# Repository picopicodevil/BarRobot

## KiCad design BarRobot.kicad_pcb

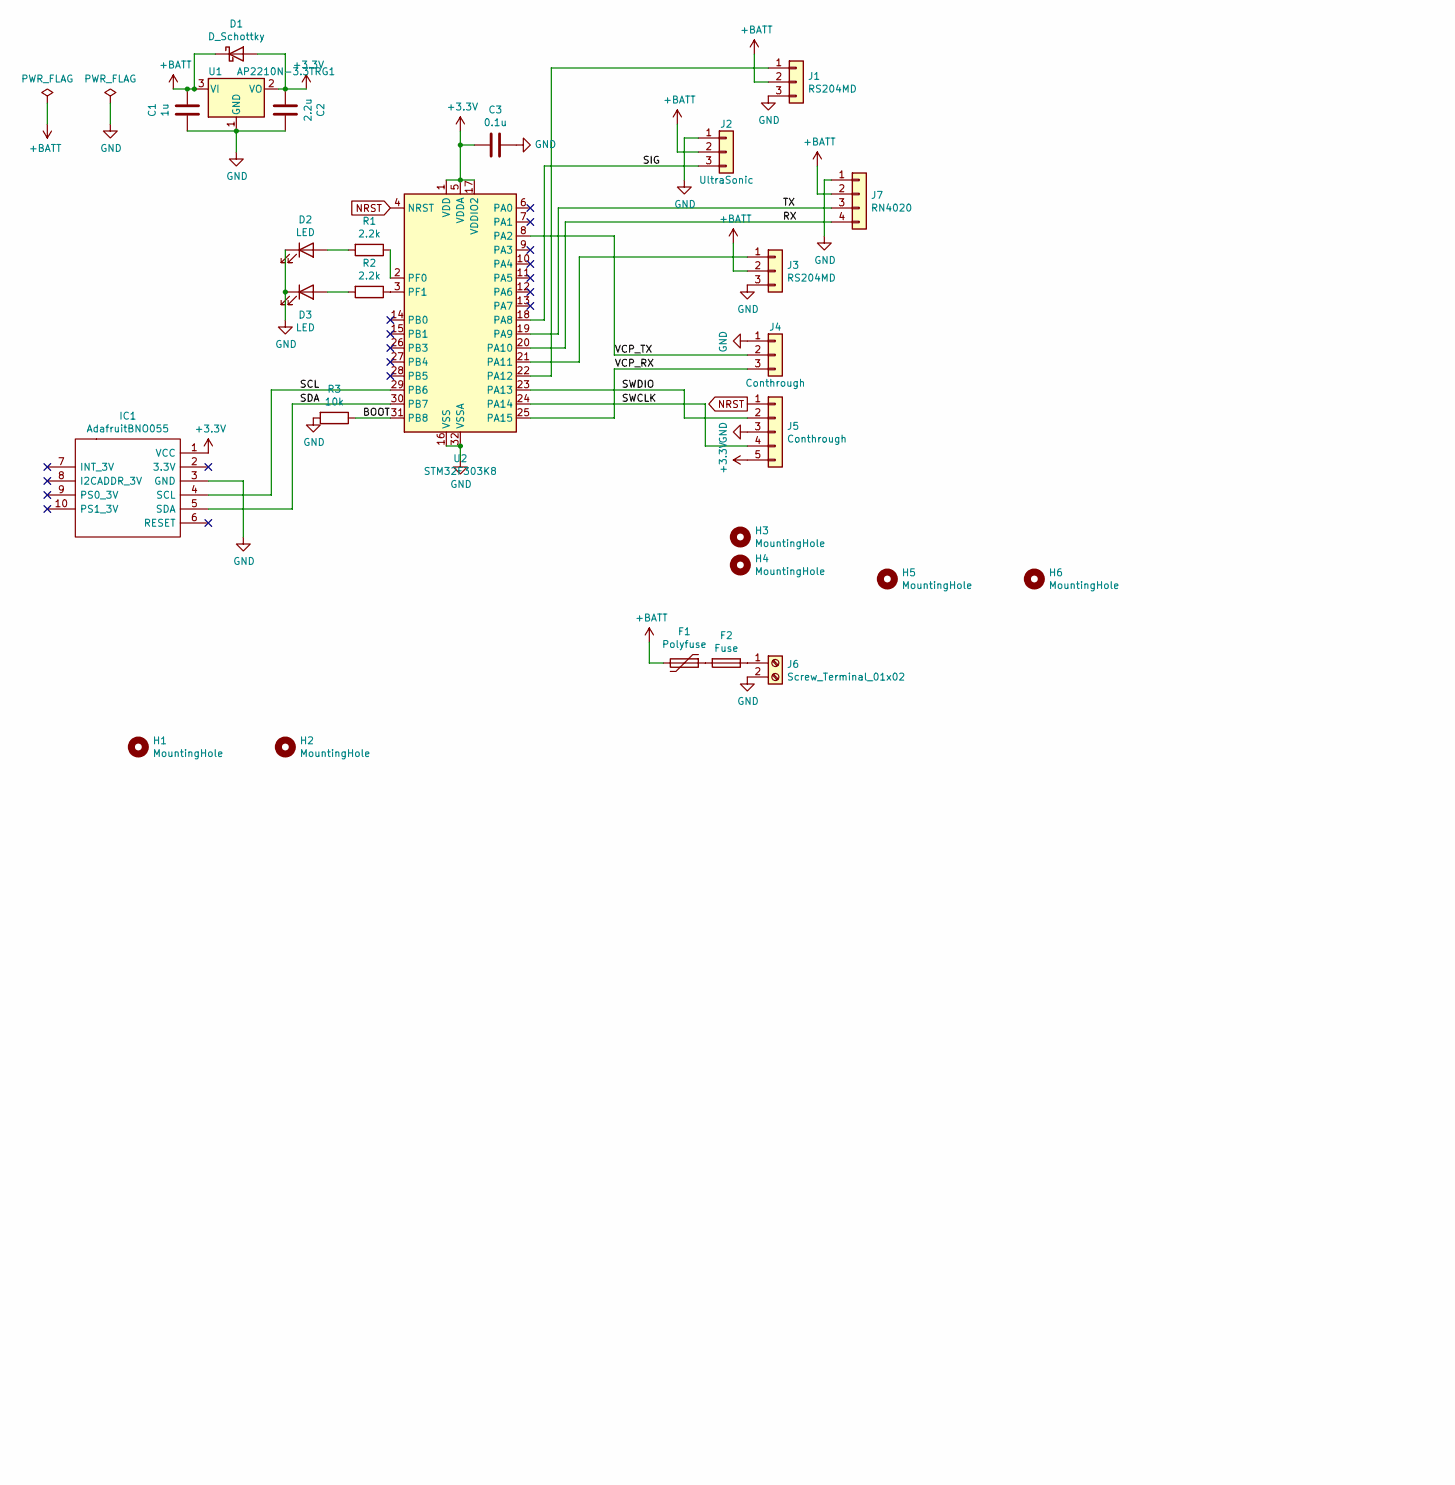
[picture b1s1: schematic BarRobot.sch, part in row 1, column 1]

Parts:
C1: 1u; C_0805_2012Metric_Pad1.15x1.40mm_HandSolder
C2: 2.2u; C_0805_2012Metric_Pad1.15x1.40mm_HandSolder
C3: 0.1u; C_0805_2012Metric_Pad1.15x1.40mm_HandSolder
D1: D_Schottky; D_0603_1608Metric_Pad1.05x0.95mm_HandSolder
D2, D3: LED; LED_0603_1608Metric_Castellated
F1: Polyfuse; Fuse_Littelfuse_395Series
F2: Fuse; MF505
H1, H2, H5, H6: MountingHole; MountingHole_1.2mm
H3, H4: MountingHole; MountingHole_3.2mm_M3
IC1: AdafruitBNO055
J1, J3: RS204MD; PinHeader_1x03_P2.54mm_Vertical
J2: UltraSonic; PinHeader_1x03_P2.54mm_Vertical
J4: Conthrough; Conthrough_1x03_P2.54mm_Vertical
J5: Conthrough; Conthrough_1x05_P2.54mm_Vertical
J6: Screw_Terminal_01x02; TerminalBlock_bornier-2_P5.08mm
J7: RN4020; PinHeader_1x04_P2.54mm_Vertical
R1, R2: 2.2k; R_0603_1608Metric_Pad1.05x0.95mm_HandSolder
R3: 10k; R_0603_1608Metric_Pad1.05x0.95mm_HandSolder
U1: AP2210N-3.3TRG1; SOT-23W_Handsoldering
U2: STM32F303K8; LQFP-32_7x7mm_P0.8mm

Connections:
+3V3: C2.2, C3.2, D1.2 (A), IC1.1 (VCC), J5.5, U1.2 (VO), U2.1 (VDD), U2.5 (VDDA), U2.17 (VDDIO2)
+BATT: C1.1, D1.1 (K), F1.2, J1.2, J2.2, J3.2, J7.2, U1.3 (VI)
/BOOT: R3.1, U2.31 (PB8)
/RX: J7.4, U2.20 (PA10)
/SCL: IC1.4 (SCL), U2.29 (PB6)
/SDA: IC1.5 (SDA), U2.30 (PB7)
/SIG: J2.3, U2.18 (PA8)
/SWCLK: J5.4, U2.24 (PA14)
/SWDIO: J5.2, U2.23 (PA13)
/TX: J7.3, U2.19 (PA9)
/VCP_RX: J4.3, U2.25 (PA15)
/VCP_TX: J4.2, U2.8 (PA2)
GND: C1.2, C2.1, C3.1, D2.1 (K), D3.1 (K), IC1.3 (GND), J1.3, J2.1, J3.3, J4.1, J5.3, J6.2, J7.1, R3.2, U1.1 (GND), U2.16 (VSS), U2.32 (VSSA)
NRST: J5.1, U2.4 (NRST)
unnamed: D2.2 (A), R1.2
unnamed: D3.2 (A), R2.2
unnamed: F1.1, F2.2
unnamed: F2.1, J6.1
unnamed: J1.1, U2.22 (PA12)
unnamed: J3.1, U2.21 (PA11)
unnamed: R1.1, U2.2 (PF0)
unnamed: R2.1, U2.3 (PF1)

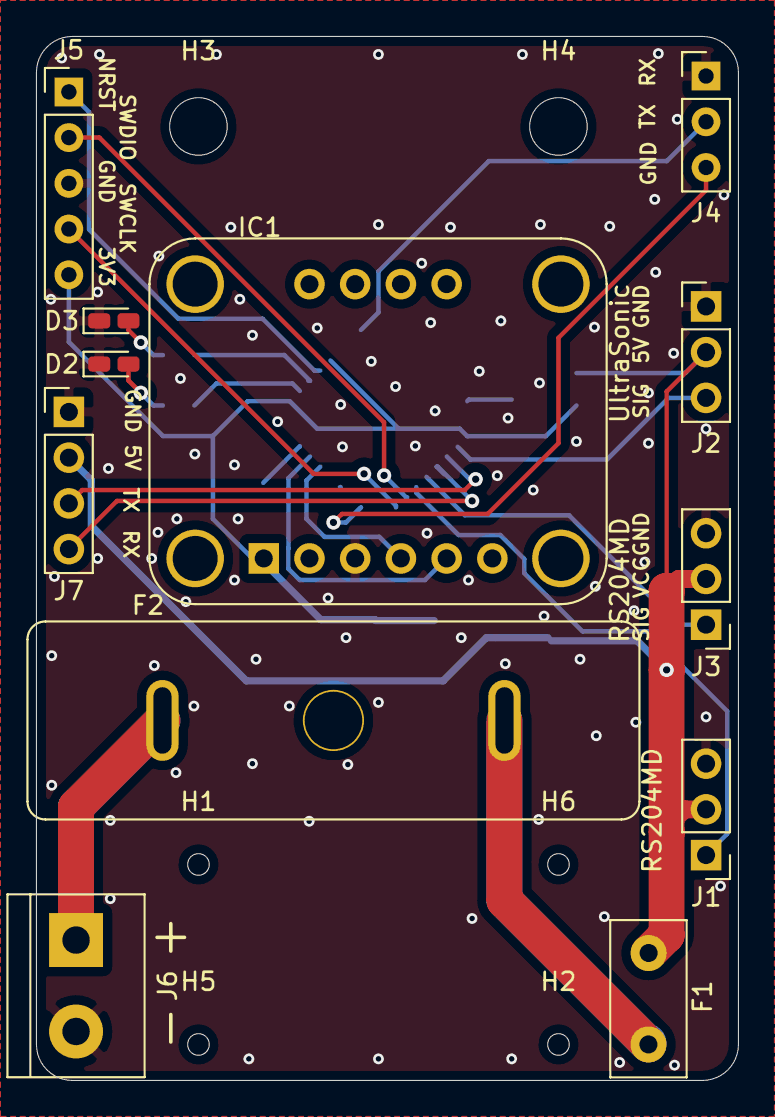
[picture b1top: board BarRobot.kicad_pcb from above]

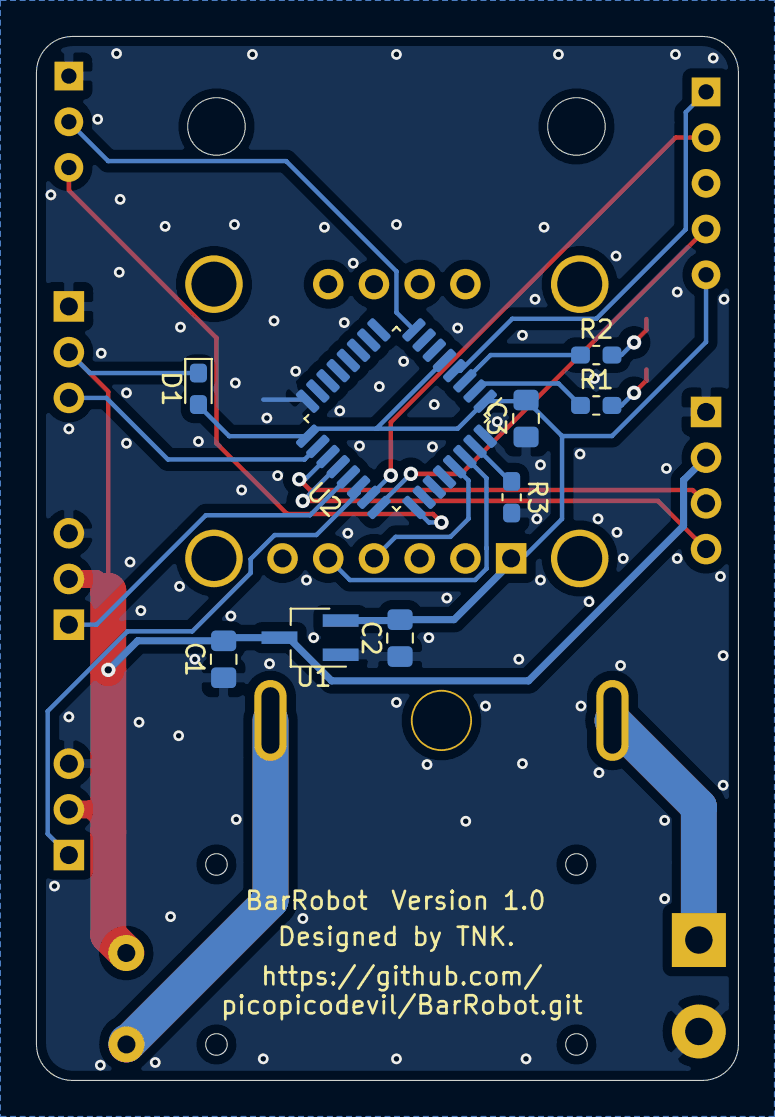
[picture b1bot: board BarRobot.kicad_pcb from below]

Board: 2 copper layers, 39.0 x 58.0 mm, 27 parts (9 on the bottom side), 22 nets.

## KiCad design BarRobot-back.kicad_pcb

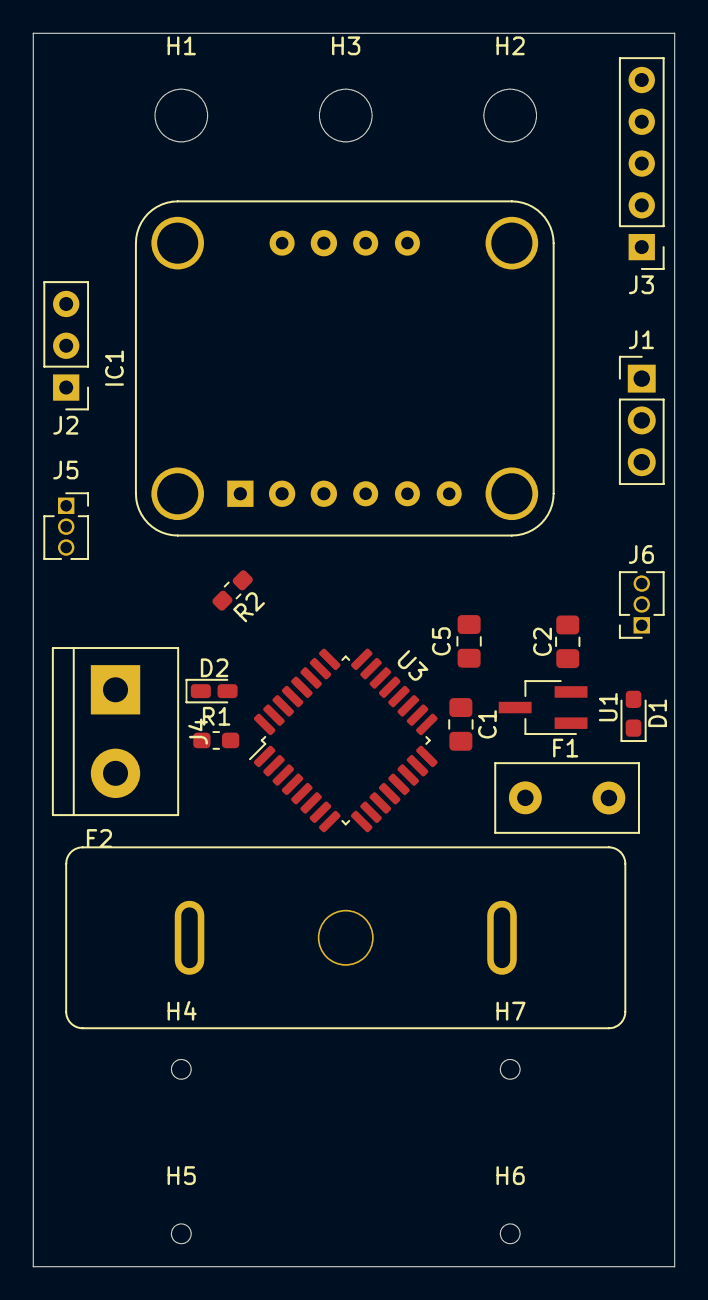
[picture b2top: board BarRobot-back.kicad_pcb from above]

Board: 2 copper layers, 39.0 x 75.0 mm, 25 parts (0 on the bottom side), 13 nets, no tracks yet.

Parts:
C1: 1u; C_0805_2012Metric_Pad1.15x1.40mm_HandSolder
C2: 2.2u; C_0805_2012Metric_Pad1.15x1.40mm_HandSolder
C5: 0.1u; C_0805_2012Metric_Pad1.15x1.40mm_HandSolder
D1: D_Schottky; D_0603_1608Metric_Pad1.05x0.95mm_HandSolder
D2: LED; LED_0603_1608Metric_Castellated
F1: Polyfuse; Fuse_Littelfuse_395Series
F2: Fuse; MF505
H1, H2, H3: MountingHole; MountingHole_3.2mm_M3
H4, H5, H6, H7: MountingHole; MountingHole_1.2mm
IC1: AdafruitBNO055
J1: UltraSonic; PinHeader_1x03_P2.54mm_Vertical
J2: Conn_01x03; Conthrough_1x03_P2.54mm_Vertical
J3: Conthrough; Conthrough_1x05_P2.54mm_Vertical
J4: Screw_Terminal_01x02; TerminalBlock_bornier-2_P5.08mm
J5, J6: RS204MD_ADH; PinSocket_1x03_P1.27mm_Vertical
R1: 2.2k; R_0603_1608Metric_Pad1.05x0.95mm_HandSolder
R2: 10k; R_0603_1608Metric_Pad1.05x0.95mm_HandSolder
U1: AP2210N-3.3TRG1; SOT-23W_Handsoldering
U3: STM32F303K8; LQFP-32_7x7mm_P0.8mm

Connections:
+3V3: C2.2, C5.2, D1.2, J3.5, U1.2, U3.1, U3.5, U3.17
/BOOT: R2.1, U3.31
/SWCLK: J3.4, U3.24
/SWDIO: J3.2, U3.23
/VCP_RX: J2.3, U3.25
/VCP_TX: J2.2, U3.8
GND: C1.2, C2.1, C5.1, J2.1, J3.3, J4.2, R1.2, R2.2, U1.1, U3.16, U3.32
NRST: J3.1, U3.4
unnamed: D2.1, R1.1
unnamed: D2.2, U3.30
unnamed: F1.1, F2.2
unnamed: F2.1, J4.1
VCC: C1.1, D1.1, F1.2, U1.3

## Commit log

2020-09-17 order Version 1.0
